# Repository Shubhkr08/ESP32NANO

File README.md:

# ESP32NANO
I made a custom Esp32 board based on ESP32-S3-WROOM-1 , it has a USB type C and i tried to keep the size of the board as small as possible and to have as much as useful pins available on the board.
<br>
<br>
## Overview
This project is a **compact 2-layer development board** based on the **ESP32-S3-WROOM-1 module**. It exposes **all usable GPIOs**, includes onboard **3.3V regulation**, and USB connectivity for easy programming and prototyping. 
The goal of this project is to **learn PCB design, microcontroller integration, and embedded programming**, while creating a versatile dev board for IoT, robotics, and electronics experiments.
## Features
- ESP32-S3-WROOM-1 module (Wi-Fi + Bluetooth 5.0)
- 2-layer compact PCB
- All GPIOs broken out (total 16+17= 33)
- USB connection for programming and power
- Onboard 3.3V voltage regulation
- Compact footprint for small projects
- Educational focus for learning MCU integration and PCB design
- ## Bill of Materials (BOM)
| Qty | Manufacturer Part Number | Description | Supplier | Unit Price (USD) | Total (USD) |
|----:|--------------------------|-------------|----------|------------------|-------------|
| 1 | ESP32-S3-WROOM-1-N16R8 | RF TXRX MODULE BT PCB TRACE SMD | DigiKey (digikey.in) | 6.56 | 6.56 |
| 1 | USB4125-GF-A | USB Type-C Receptacle 6-Pin SMD | DigiKey (digikey.in) | 0.57 | 0.57 |
| 5 | AMS1117-3.3 | 3.3V Linear Regulator | DigiKey (digikey.in) | 0.27 | 1.35 |
| 2 | PTS810SJG250SMTR LFS | Tactile Switch SPST-NO | DigiKey (digikey.in) | 0.57 | 1.14 |
| 1 | RS0805CT-1000GN-90TRD | 100Ω RF Resistor | DigiKey (digikey.in) | 2.90 | 2.90 |
| 1 | T529P106M010AAE200 | 10µF Tantalum Capacitor | DigiKey (digikey.in) | 1.26 | 1.26 |
| 1 | T529P226M010AAE200 | 22µF Tantalum Capacitor | DigiKey (digikey.in) | 1.32 | 1.32 |
| 1 | CL21B105KBFNNNE | 1µF Ceramic Capacitor | DigiKey (digikey.in) | 0.08 | 0.08 |
| 1 | CL21A226MAYNNNE | 22µF Ceramic Capacitor | DigiKey (digikey.in) | 0.08 | 0.08 |
| 2 | C0805C104K5RACTU | 0.1µF Ceramic Capacitor | DigiKey (digikey.in) | 0.08 | 0.16 |
| 2 | RC0805JR-075K1L | 5.1kΩ Resistor | DigiKey (digikey.in) | 0.10 | 0.20 |
| 1 | RC0805JR-0710KL | 10kΩ Resistor | DigiKey (digikey.in) | 0.10 | 0.10 |

### 🖨️ PCB & Shipping

- **DigiKey Shipping:** $20.00  
- **PCB + Stencil + Shipping:** $28.81 (JLCPCB)  
- **PCB Manufacturer:** JLCPCB — https://jlcpcb.com/

### 💰 Cost Summary

- **Components Total:** $21.72  
- **Shipping + PCB:** $48.81  
- **Estimated Total Cost:** **$70.53 USD**
## Schematic & PCB

- ## 3d Render<br><br>

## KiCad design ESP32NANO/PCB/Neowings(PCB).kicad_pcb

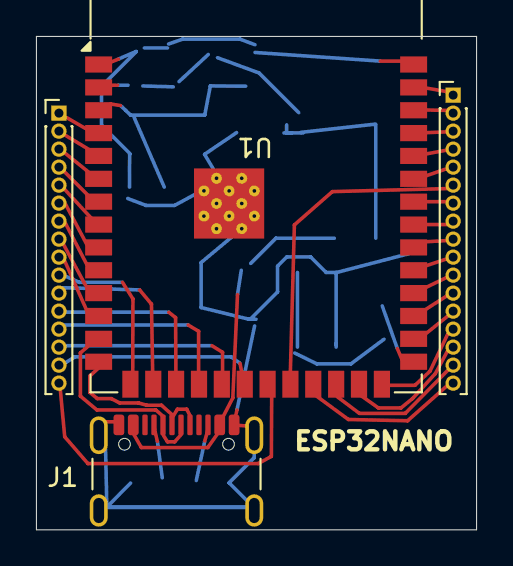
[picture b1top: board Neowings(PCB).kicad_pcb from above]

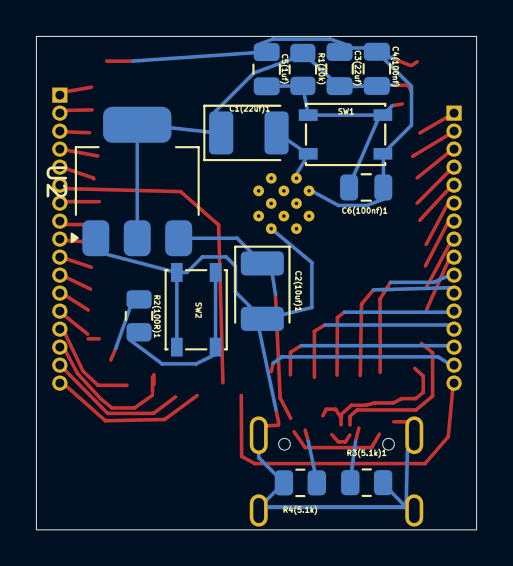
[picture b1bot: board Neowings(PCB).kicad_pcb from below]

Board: 2 copper layers, 24.5 x 27.4 mm, 17 parts (13 on the bottom side), 43 nets.

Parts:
C1(22uf)1, C2(10uf)1: C_Polarized; CP_EIA-3528-21_Kemet-B
C3(22uf), C4(100nf), C5(1uf), C6(100nf)1: C; C_0805_2012Metric
IO1: Conn_01x16_Pin; PinHeader_1x16_P1.00mm_Vertical
J1: USB_C_Receptacle_USB2.0_16P; USB_C_Receptacle_GCT_USB4105-xx-A_16P_TopMnt_Horizontal
J3: Conn_01x17_Pin; PinHeader_1x17_P1.00mm_Vertical
R1(10k), R2(100R)1, R3(5.1k)1, R4(5.1k): R; R_0805_2012Metric
SW1, SW2: SW_Push; SW_SPST_PTS810
U1: ESP32-S3-WROOM-1
U2: AMS1117-3.3; SOT-223-3_TabPin2

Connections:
+3.3V: C1(22uf)1.1, C3(22uf).1, C4(100nf).1, R1(10k).1, U1.2 (3V3), U2.2 (VO)
+5V: C2(10uf)1.1, J1.A4 (VBUS), J1.A9 (VBUS), J1.B4 (VBUS), J1.B9 (VBUS), U2.3 (VI)
BOOT: R2(100R)1.1, U1.27 (IO0)
D+: J1.A6 (D+), J1.B6 (D+), U1.14 (USB_D+)
D-: J1.A7 (D-), J1.B7 (D-), U1.13 (USB_D-)
EN: C5(1uf).1, C6(100nf)1.1, R1(10k).2, SW1.1, U1.3 (EN)
GND: C1(22uf)1.2, C2(10uf)1.2, C3(22uf).2, C4(100nf).2, C5(1uf).2, C6(100nf)1.2, J1.A1 (GND), J1.A12 (GND), J1.B1 (GND), J1.B12 (GND), J1.S1 (SHIELD), R3(5.1k)1.2, R4(5.1k).2, SW1.2, SW2.2, U1.1 (GND), U1.40 (GND), U1.41 (GND), U2.1 (GND)
unnamed: IO1.1, U1.4 (IO4)
unnamed: IO1.2, U1.5 (IO5)
unnamed: IO1.3, U1.6 (IO6)
unnamed: IO1.4, U1.7 (IO7)
unnamed: IO1.5, U1.8 (IO15)
unnamed: IO1.6, U1.9 (IO16)
unnamed: IO1.7, U1.10 (IO17)
unnamed: IO1.8, U1.11 (IO18)
unnamed: IO1.9, U1.12 (IO8)
unnamed: IO1.10, U1.15 (IO3)
unnamed: IO1.11, U1.16 (IO46)
unnamed: IO1.12, U1.17 (IO9)
unnamed: IO1.13, U1.18 (IO10)
unnamed: IO1.14, U1.19 (IO11)
unnamed: IO1.15, U1.20 (IO12)
unnamed: IO1.16, U1.21 (IO13)
unnamed: J1.A5 (CC1), R3(5.1k)1.1
unnamed: J1.B5 (CC2), R4(5.1k).1
unnamed: J3.1, U1.39 (IO1)
unnamed: J3.2, U1.38 (IO2)
unnamed: J3.3, U1.37 (TXD0)
unnamed: J3.4, U1.36 (RXD0)
unnamed: J3.5, U1.35 (IO42)
unnamed: J3.6, U1.22 (IO14)
unnamed: J3.7, U1.34 (IO41)
unnamed: J3.8, U1.33 (IO40)
unnamed: J3.9, U1.32 (IO39)
unnamed: J3.10, U1.31 (IO38)
unnamed: J3.11, U1.30 (IO37)
unnamed: J3.12, U1.29 (IO36)
unnamed: J3.13, U1.28 (IO35)
unnamed: J3.14, U1.26 (IO45)
unnamed: J3.15, U1.25 (IO48)
unnamed: J3.16, U1.24 (IO47)
unnamed: J3.17, U1.23 (IO21)
unnamed: R2(100R)1.2, SW2.1
